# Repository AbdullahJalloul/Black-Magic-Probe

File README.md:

# ISO Black Magic Probe

**Black Magic Probe hardware features:**

*  On board implementation of JTAG (Joint Test Access Group) protocol
*  On board implementation of the SWD (Serial Wire Debug) protocol
*  High speed data interface to the Device Under Test 4.5MBit
*  On board implementation of the GNU Debugger Server protocol (no need for OpenOCD) works with stock arm-none-eabi-gdb (no patches or plugins needed)
*  Automatic detection of the Device Under Test (no need for config files)
*  Frontend Level shifter. Usable with targets that run on voltages as low as 1.7V and as high as 5V.
*  There is experimental support for Cortex-A (ARMv7-A architecture). This is being used with success on Xilinx Zynq-7000 SoC (Dual-core Cortex-A9) and Raspberry Pi 2 (Quad-core Cortex-A7).
*  Semihosting IO support (allows execution of print, read, open, system calls on the host through the JTAG/SWD interface)
*  Interface to the host computer is a standard USB CDC ACM device (virtual serial port), which does not require special drivers on Linux or MacOS.
*  Auxiliary UART interface. Black Magic Probe can be used as a USB to Serial adapter at the same time together with the JTAG/SWD interface.
*  Implements USB DFU class for easy firmware upgrade as updates become available.
*  Works with Windows, Linux and MacOS environments.

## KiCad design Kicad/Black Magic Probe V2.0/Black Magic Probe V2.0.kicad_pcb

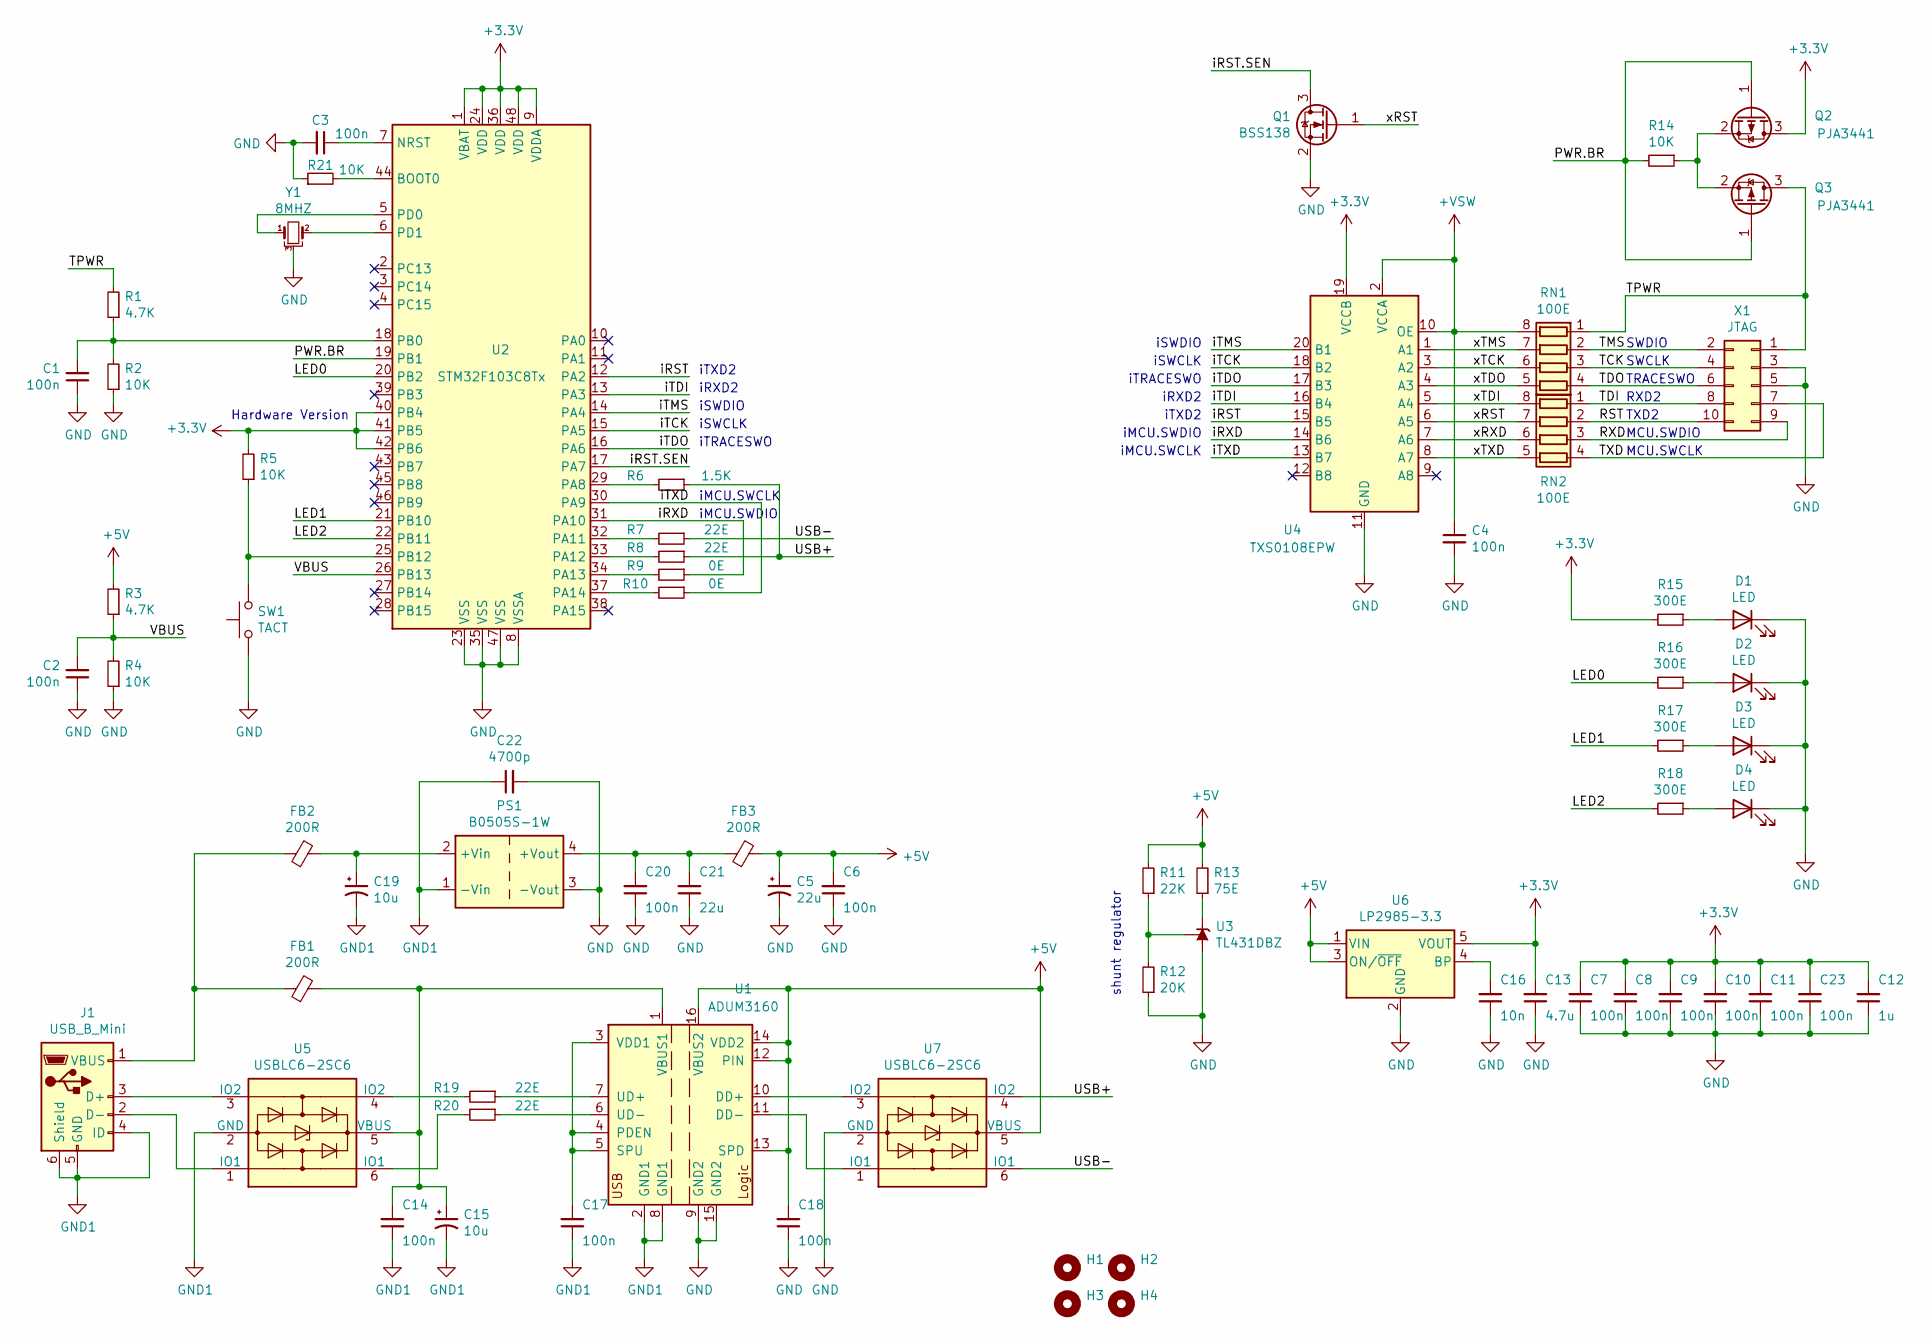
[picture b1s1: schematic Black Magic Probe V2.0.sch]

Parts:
C1, C2, C3, C4, C6, C7, C8, C9, C10, C11, C14, C17, C18, C20, C23: 100n; C_0805_2012Metric
C5, C21: 22u; C_1206_3216Metric
C12: 1u; C_0805_2012Metric
C13: 4.7u; C_0805_2012Metric
C15: 10u; CP_EIA-3216-10_Kemet-I
C16: 10n; C_0805_2012Metric
C19: 10u; CP_EIA-3216-18_Kemet-A
C22: 4700p; C_Disc_D7.5mm_W2.5mm_P5.00mm
D1, D2, D3, D4: LED; LED_0805_2012Metric
FB1, FB2, FB3: 200R; L_0805_2012Metric
H1, H2, H3, H4: MountingHole; MountingHole_2.2mm_M2
J1: USB_B_Mini; USB_Mini-B_Lumberg_2486_01_Horizontal
PS1: B0505S-1W; Converter_DCDC_Murata_MEE1SxxxxSC_THT
Q1: BSS138; SOT-23
Q2, Q3: PJA3441; SOT-23
R1, R3: 4.7K; R_0805_2012Metric
R2, R4, R5, R14, R21: 10K; R_0805_2012Metric
R6: 1.5K; R_0805_2012Metric
R7, R8, R19, R20: 22E; R_0805_2012Metric
R9, R10: 0E; R_0805_2012Metric
R11: 22K; R_0805_2012Metric
R12: 20K; R_0805_2012Metric
R13: 75E; R_1206_3216Metric
R15, R16, R17, R18: 300E; R_0805_2012Metric
RN1, RN2: 100E; R_Array_Convex_4x0603
SW1: TACT; SW_SPST_PTS645
U1: ADUM3160; SOIC-16W_7.5x10.3mm_P1.27mm
U2: STM32F103C8Tx; LQFP-48_7x7mm_P0.5mm
U3: TL431DBZ; SOT-23
U4: TXS0108EPW; SSOP-20_4.4x6.5mm_P0.65mm
U5, U7: USBLC6-2SC6; SOT-23-6
U6: LP2985-3.3; SOT-23-5
X1: JTAG; PinHeader_2x05_P2.54mm_Vertical
Y1: 8MHZ; CSTCE8M00G52

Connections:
+3V3: C7.2, C8.2, C9.2, C10.2, C11.2, C12.2, C13.2, C23.2, Q2.3 (D), R5.2, R15.2, U2.1 (VBAT), U2.9 (VDDA), U2.24 (VDD), U2.36 (VDD), U2.40 (PB4), U2.41 (PB5), U2.42 (PB6), U2.48 (VDD), U4.19 (VCCB), U6.5 (VOUT)
+5V: C5.1, C6.2, C18.2, FB3.2, R3.2, R11.2, R13.2, U1.12 (PIN), U1.13 (SPD), U1.14 (VDD2), U1.16 (VBUS2), U6.1 (VIN), U6.3 (ON/~OFF~), U7.5 (VBUS)
+VSW: C4.1, RN1.8 (R1.2), U4.2 (VCCA), U4.10 (OE)
/LED0: R16.2, U2.20 (PB2)
/LED1: R17.2, U2.21 (PB10)
/LED2: R18.2, U2.22 (PB11)
/PWR.BR: Q2.1 (G), Q3.1 (G), R14.2, U2.19 (PB1)
/RST: RN2.2 (R2.1), X1.10
/RXD: RN2.3 (R3.1), X1.9
/TCK: RN1.3 (R3.1), X1.4
/TDI: RN2.1 (R1.1), X1.8
/TDO: RN1.4 (R4.1), X1.6
/TMS: RN1.2 (R2.1), X1.2
/TPWR: Q3.3 (D), R1.2, RN1.1 (R1.1), X1.1
/TXD: RN2.4 (R4.1), X1.7
/USB+: R6.1, R8.1, U7.4 (IO2)
/USB-: R7.1, U7.6 (IO1)
/VBUS: C2.2, R3.1, R4.2, U2.26 (PB13)
/iRST: U2.12 (PA2), U4.15 (B5)
/iRST.SEN: Q1.3 (D), U2.17 (PA7)
/iRXD: R9.1, U2.31 (PA10), U4.14 (B6)
/iTCK: U2.15 (PA5), U4.18 (B2)
/iTDI: U2.13 (PA3), U4.16 (B4)
/iTDO: U2.16 (PA6), U4.17 (B3)
/iTMS: U2.14 (PA4), U4.20 (B1)
/iTXD: R10.1, U2.30 (PA9), U4.13 (B7)
/xRST: Q1.1 (G), RN2.7 (R2.2), U4.6 (A5)
/xRXD: RN2.6 (R3.2), U4.7 (A6)
/xTCK: RN1.6 (R3.2), U4.3 (A2)
/xTDI: RN2.8 (R1.2), U4.5 (A4)
/xTDO: RN1.5 (R4.2), U4.4 (A3)
/xTMS: RN1.7 (R2.2), U4.1 (A1)
/xTXD: RN2.5 (R4.2), U4.8 (A7)
GND: C1.1, C2.1, C3.2, C4.2, C5.2, C6.1, C7.1, C8.1, C9.1, C10.1, C11.1, C12.1, C13.1, C16.1, C18.1, C20.1, C21.1, C22.2, C23.1, D1.1 (K), D2.1 (K), D3.1 (K), D4.1 (K), PS1.3 (-Vout), Q1.2 (S), R2.1, R4.1, R12.1, R21.1, SW1.1, U1.9 (GND2), U1.15 (GND2), U2.8 (VSSA), U2.23 (VSS), U2.35 (VSS), U2.47 (VSS), U3.3 (A), U4.11 (GND), U6.2 (GND), U7.2 (GND), X1.3, X1.5, Y1.3
GND1: C14.1, C15.2, C17.1, C19.2, C22.1, J1.4 (ID), J1.5 (GND), J1.6 (Shield), PS1.1 (-Vin), U1.2 (GND1), U1.8 (GND1), U5.2 (GND)
unnamed: C1.2, R1.1, R2.2, U2.18 (PB0)
unnamed: C3.1, U2.7 (NRST)
unnamed: C14.2, C15.1, FB1.2, U1.1 (VBUS1), U5.5 (VBUS)
unnamed: C16.2, U6.4 (BP)
unnamed: C17.2, U1.3 (VDD1), U1.4 (PDEN), U1.5 (SPU)
unnamed: C19.1, FB2.2, PS1.2 (+Vin)
unnamed: C20.2, C21.2, FB3.1, PS1.4 (+Vout)
unnamed: D1.2 (A), R15.1
unnamed: D2.2 (A), R16.1
unnamed: D3.2 (A), R17.1
unnamed: D4.2 (A), R18.1
unnamed: FB1.1, FB2.1, J1.1 (VBUS)
unnamed: J1.2 (D-), U5.1 (IO1)
unnamed: J1.3 (D+), U5.3 (IO2)
unnamed: Q2.2 (S), Q3.2 (S), R14.1
unnamed: R5.1, SW1.2, U2.25 (PB12)
unnamed: R6.2, U2.29 (PA8)
unnamed: R7.2, U2.32 (PA11)
unnamed: R8.2, U2.33 (PA12)
unnamed: R9.2, U2.34 (PA13)
unnamed: R10.2, U2.37 (PA14)
unnamed: R11.1, R12.2, U3.2 (REF)
unnamed: R13.1, U3.1 (K)
unnamed: R19.1, U1.7 (UD+)
unnamed: R19.2, U5.4 (IO2)
unnamed: R20.1, U1.6 (UD-)
unnamed: R20.2, U5.6 (IO1)
unnamed: R21.2, U2.44 (BOOT0)
unnamed: U1.10 (DD+), U7.3 (IO2)
unnamed: U1.11 (DD-), U7.1 (IO1)
unnamed: U2.5 (PD0), Y1.1
unnamed: U2.6 (PD1), Y1.2

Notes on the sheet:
SWDIO
SWCLK
TRACESWO
RXD2
TXD2
MCU.SWDIO
MCU.SWCLK
iMCU.SWCLK
iMCU.SWDIO
iSWDIO
iSWCLK
iTRACESWO
iRXD2
iTXD2
Hardware Version
shunt regulator

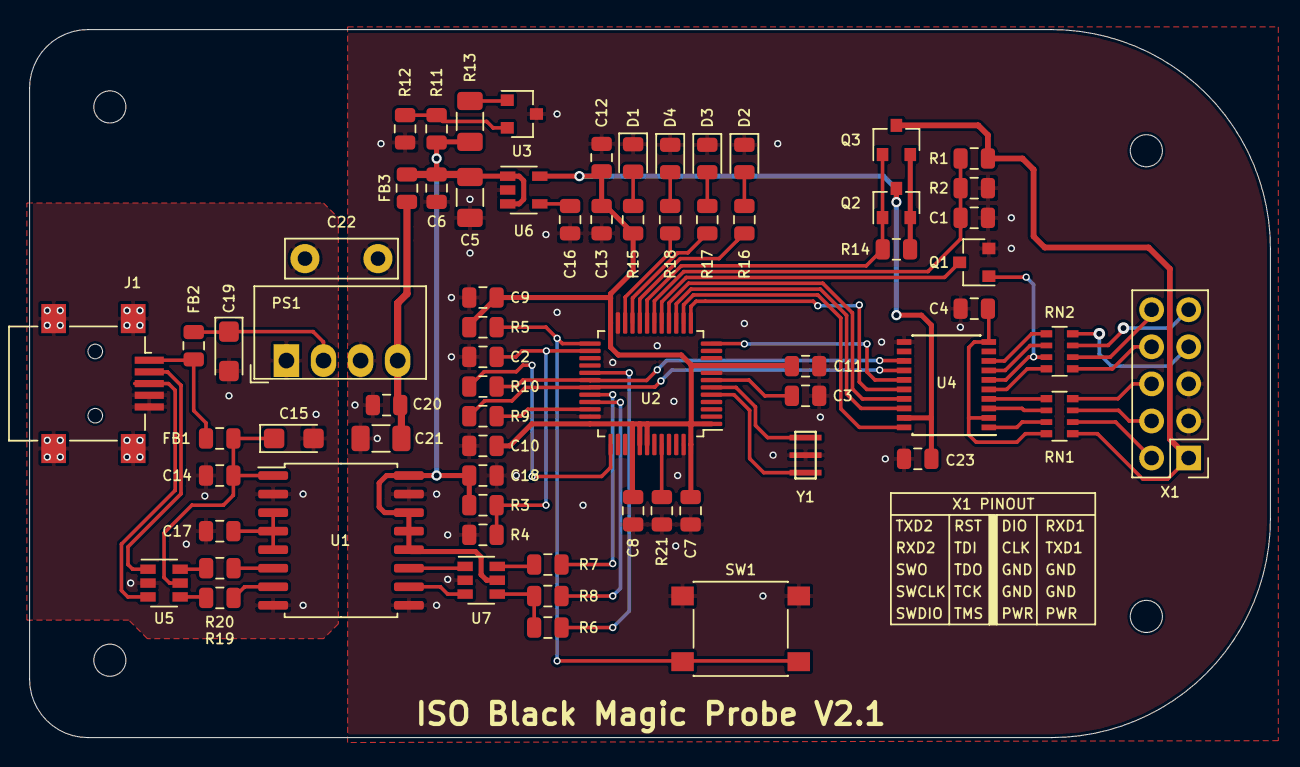
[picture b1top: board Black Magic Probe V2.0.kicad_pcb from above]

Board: 2 copper layers, 85.0 x 48.5 mm, 72 parts (0 on the bottom side), 67 nets.

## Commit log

2022-03-28 Update PCB
2022-03-28 add sch and PCB
